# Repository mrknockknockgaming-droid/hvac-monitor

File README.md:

# Fullscope: continuous HVAC diagnostics

Fullscope monitors a home's heat pump or air conditioner continuously, the way a technician
would with gauges on it, and tells the contractor and the homeowner when something is going
wrong, before it becomes a no-cool call.

Two small ESP32 monitors sit on the equipment:
- **Outdoor:** refrigerant pressures, line temperatures, outdoor air.
- **Indoor:** supply and return air.

Both read which calls the thermostat is making. A cloud service turns their readings into
superheat, subcooling, delta-T and other checks, and shows them in a web app with two views:
- a **technician view** with live trends and diagnostics;
- a **homeowner view** in plain language.

## Status (October 2026)

| Part | State |
|---|---|
| Node firmware (outdoor + indoor) | v0.2.0 built; both dev boards online running 0.1.0, 0.2.0 goes on at board bring-up |
| Carrier boards (rev A, KiCad) | Arrived and assembled; all sensors arrived, enclosures next |
| Cloud + web app | Working locally (SQLite) and in Docker (TimescaleDB); production setup ready to deploy |
| Contractor demo | Seven scripted homes for customer interviews |
| Display thermostat (add-on) | Cloud side, screen and firmware written and tested on the PC; no hardware yet |
| Electrical module (add-on) | Diagnostics written; no hardware yet |
| 900 MHz LoRa radio | Designed and written (nodes, gateway, thermostat as gateway); waiting on a range test |

The full plan is in [project-files/1-plans/roadmap.md](project-files/1-plans/roadmap.md).

## How it fits together

```
 outdoor node ─┐                       ┌─ web app: homeowner + technician views, fleet page
 indoor node  ─┼─ WiFi (or LoRa via ─▶ MQTT broker ─▶ cloud: ingest → diagnostics → alerts
 thermostat   ─┘   a gateway)                          (FastAPI, SQLite / TimescaleDB)
                                                       └─ email alerts, thermostat config + display feed
```

- The nodes publish JSON on `hvac/<site>/<node>/{telemetry,status,reply}` and take
  calibration commands on `.../cmd`.
- The cloud judges each check only when it can be judged, for example refrigerant after
  10 minutes of steady running. A problem that lasts 5 minutes raises an alert.
- The optional display thermostat runs all its control and safety logic on the device itself,
  so heating and cooling never depend on the internet.

## What's where

| Folder | What it is |
|---|---|
| [hvac-firmware](hvac-firmware) | ESP32 firmware for the outdoor and indoor nodes (PlatformIO) |
| [hvac-cloud](hvac-cloud) | Cloud: MQTT ingest, diagnostics, alerts, REST API, the Fullscope web app, contractor demo, Docker / production setup ([DEPLOY.md](hvac-cloud/DEPLOY.md)) |
| [hvac-monitor-app](hvac-monitor-app) | PC dashboard for bench work with one system |
| [hardware](hardware) | Rev A carrier boards (KiCad, fabrication files, schematic PDFs) |
| [docs](docs) | Wiring schematics and carrier-board notes (HTML) |
| [thermostat](thermostat) | Display thermostat: design ([README](thermostat/README.md)) and firmware for the Waveshare ESP32-S3 4.3" board |
| [electrical](electrical) | Electrical monitoring module: design and diagnostic rules |
| [radio](radio) | 900 MHz LoRa: FCC research, frame format, Python reference, C++ library, gateway, range test |
| [design](design) | Fullscope design system, mockups and logos |
| [project-files](project-files) | Roadmap, contractor interview kit, parts list, screenshots, branding |
| [_archive](_archive) | Early prototypes, kept for reference |

[CLAUDE.md](CLAUDE.md) is the detailed, up-to-date technical overview of the whole project.

## Running it

**On Windows, the quick way:** `start-hvac.bat` (the Desktop "HVAC Monitor" shortcut) starts
three things:
- the MQTT broker;
- the PC dashboard on http://localhost:8080;
- the cloud with its web app on http://localhost:8000.

**Cloud only, for development:**

```powershell
cd hvac-cloud
python -m venv .venv
.venv\Scripts\python.exe -m pip install -r requirements-dev.txt
.venv\Scripts\python.exe -m pytest -q
```

Then follow [hvac-cloud/README.md](hvac-cloud/README.md) to create an account and system and
start the ingest worker and API.

**The contractor demo:** after the cloud is running, `hvac-cloud\start-demo.bat` creates a demo
contractor account with seven homes acting out common faults. The sign-ins are saved to
`hvac-cloud\demo-login.txt`.

**Firmware:** copy `include/config.example.h` to `include/config.h`, fill in WiFi and the
broker, then build and flash with PlatformIO:

```powershell
cd hvac-firmware
pio run -e outdoor -t upload
```

See [hvac-firmware/README.md](hvac-firmware/README.md) for calibration and the command list.

## Tests

| Where | Command | What it checks |
|---|---|---|
| `hvac-cloud` | `.venv\Scripts\python.exe -m pytest -q` | Cloud, diagnostics, alerts, accounts, thermostat, demo |
| `thermostat/firmware` | `pio test -e native` | The thermostat's C++ controller replayed against the Python reference |
| `radio/lora` | `pio test -e native` | LoRa frames and encryption, byte for byte against the Python reference |
| `radio` | `.venv\Scripts\python.exe -m pytest -q` | The Python frame format reference |

The native PlatformIO tests need a host C++ compiler, for example MSYS2 `ucrt64` on the PATH.

## Safety

The monitors are low-voltage (24 VAC from the equipment's control circuit). Never connect a
board to USB and 24 VAC at the same time. The electrical module and the thermostat touch more
than that, and their READMEs cover what is needed before either goes near real equipment
(isolation, qualified installation, UL 60730 / 61010). Readings are diagnostic inferences, not
confirmed diagnoses.

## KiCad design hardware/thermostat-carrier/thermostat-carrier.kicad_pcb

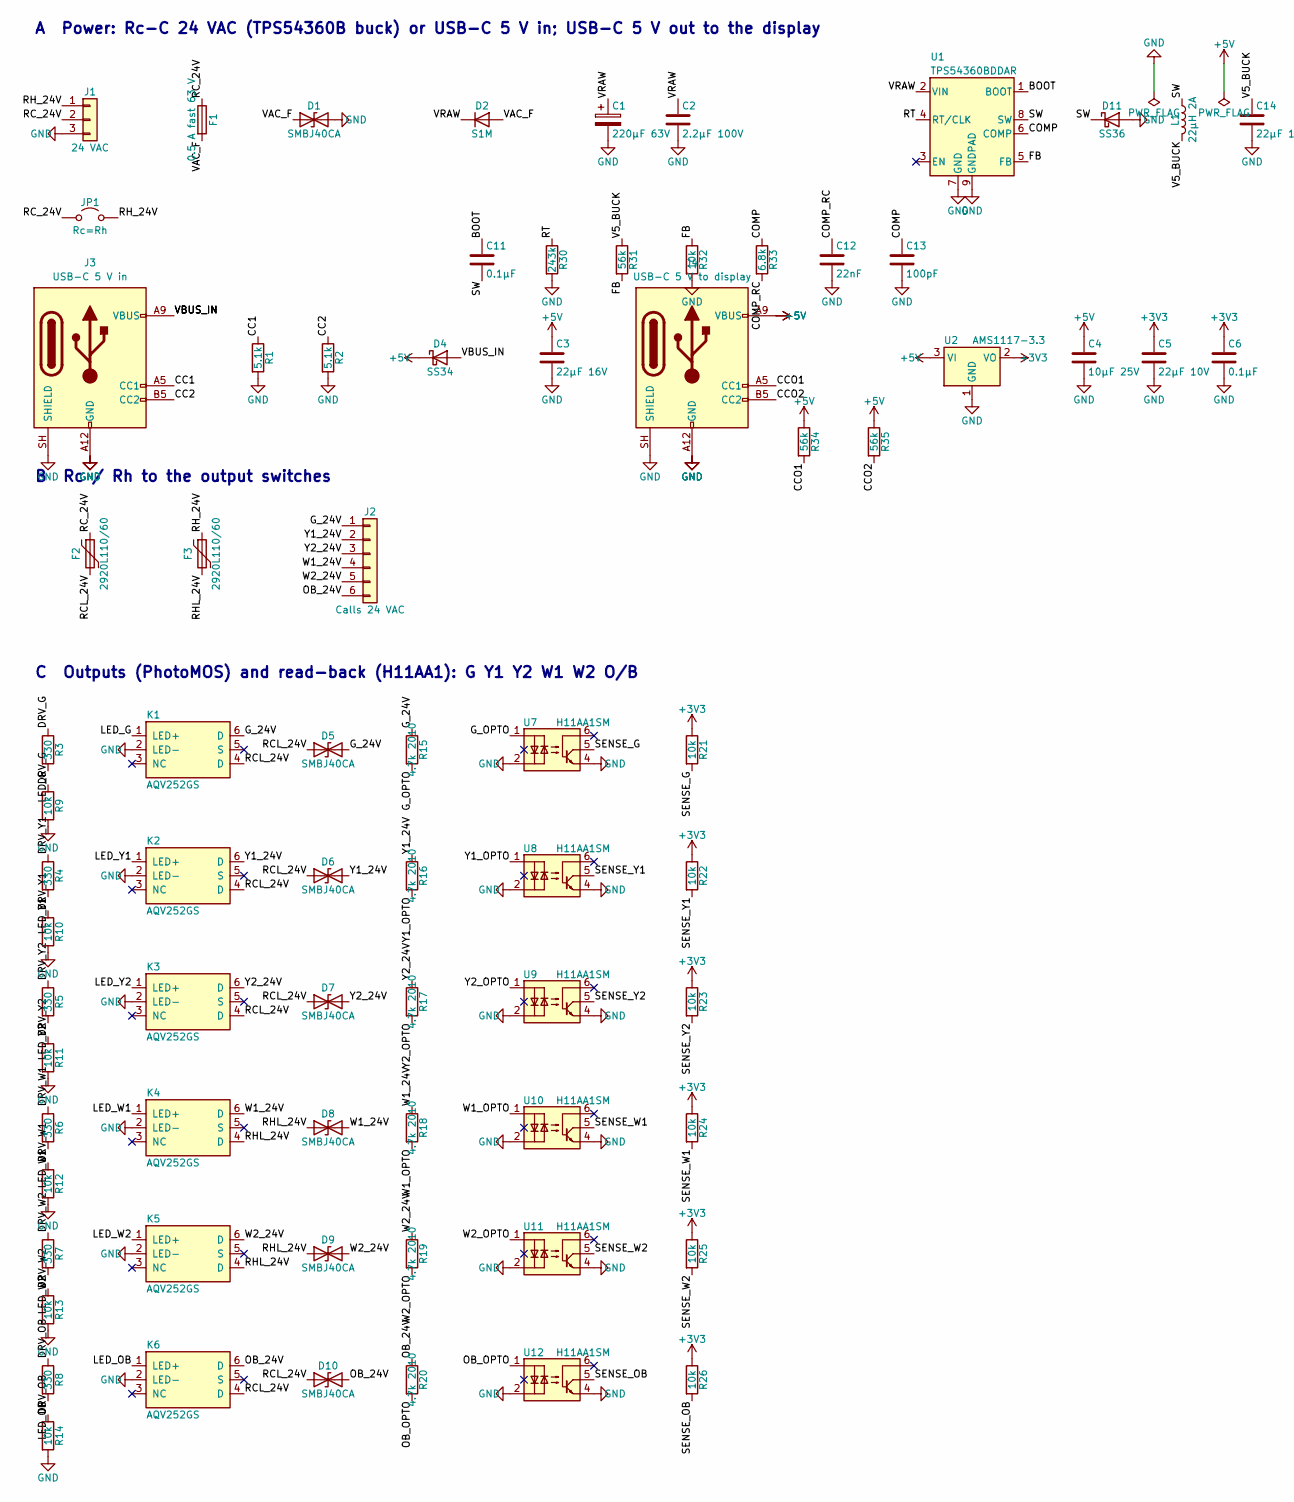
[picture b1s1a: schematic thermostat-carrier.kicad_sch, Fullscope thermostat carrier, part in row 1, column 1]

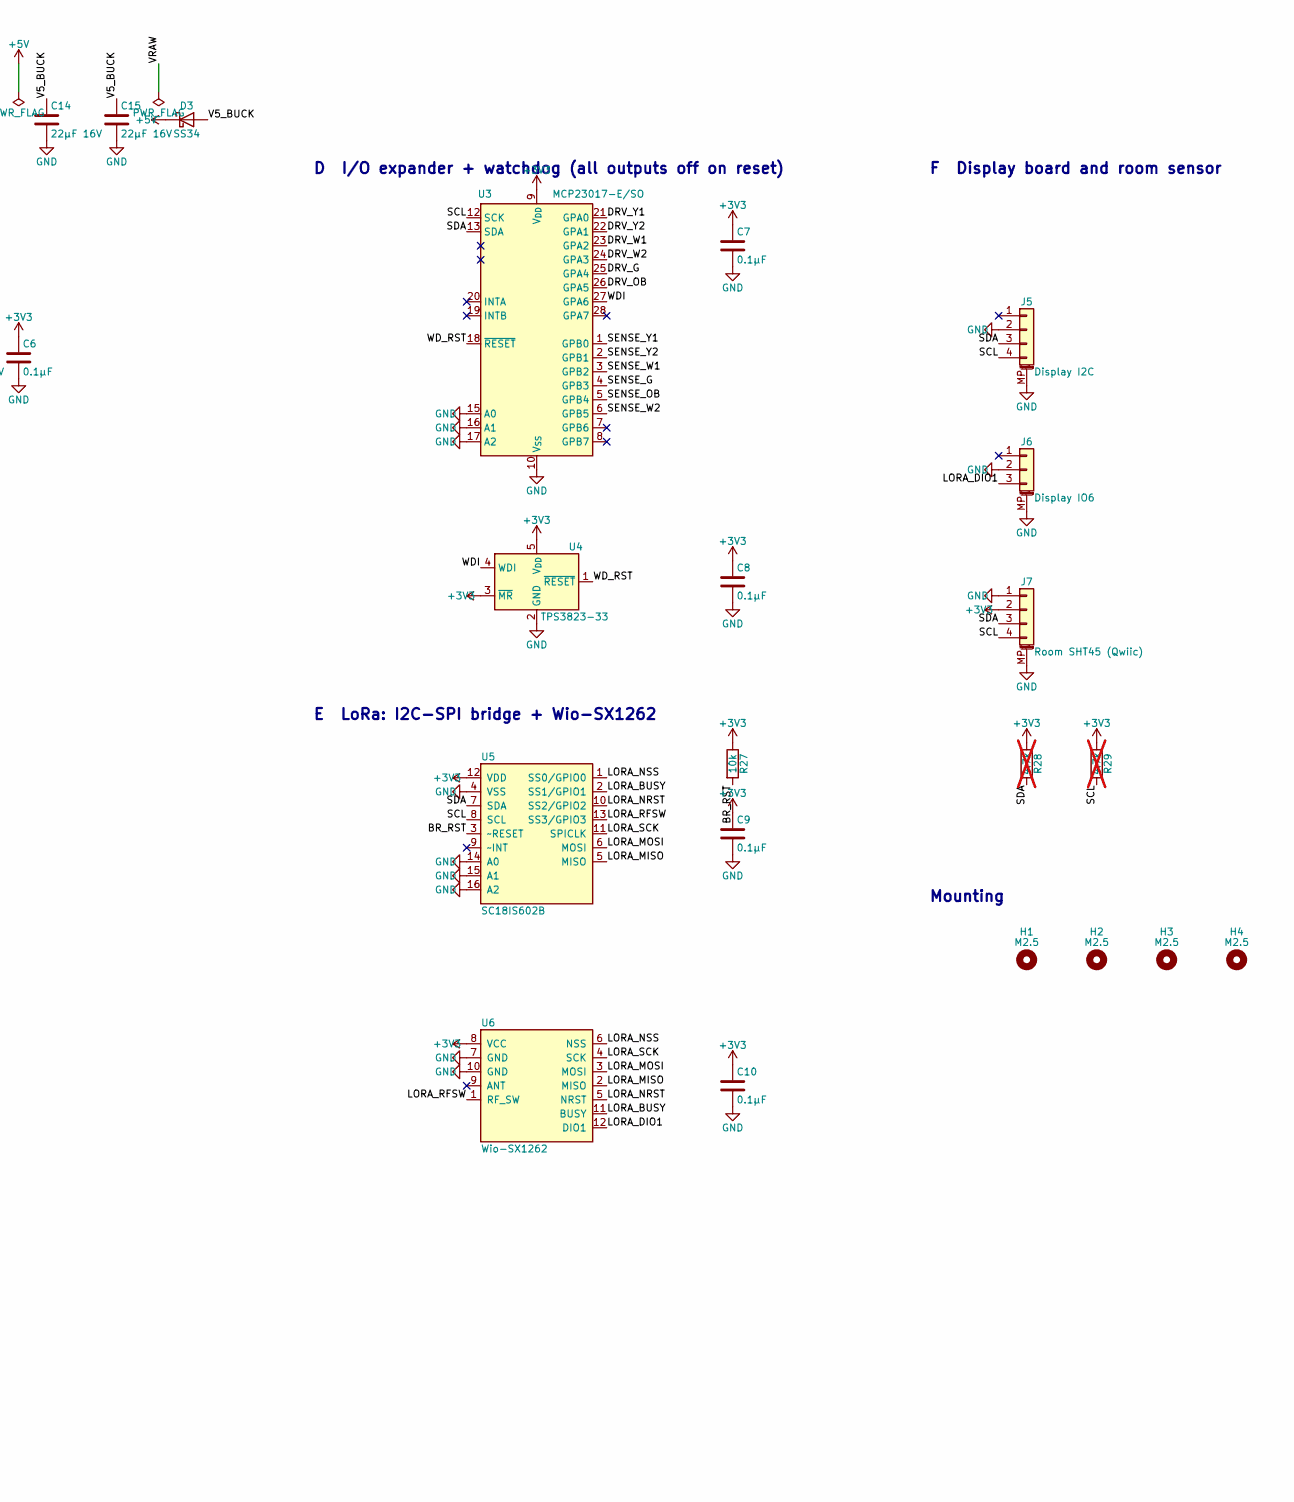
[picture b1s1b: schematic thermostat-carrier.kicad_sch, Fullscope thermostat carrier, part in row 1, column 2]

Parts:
C1: 220µF 63V; CP_Elec_10x10.5
C2: 2.2µF 100V; C_1210_3225Metric
C3, C14, C15: 22µF 16V; C_1206_3216Metric
C4: 10µF 25V; C_0805_2012Metric
C5: 22µF 10V; C_0805_2012Metric
C6, C7, C8, C9, C10, C11: 0.1µF; C_0805_2012Metric
C12: 22nF; C_0805_2012Metric
C13: 100pF; C_0805_2012Metric
D1, D5, D6, D7, D8, D9, D10: SMBJ40CA; D_SMB
D2: S1M; D_SMA
D3, D4: SS34; D_SMA
D11: SS36; D_SMA
F1: 0.5 A fast 63 V; Fuse_1206_3216Metric
F2, F3: 2920L110/60; Fuse_2920_7451Metric
H1, H2, H3, H4: M2.5; MountingHole_2.7mm_M2.5_DIN965
J1: 24 VAC; PhoenixContact_MCV_1,5_3-G-3.5_1x03_P3.50mm_Vertical
J2: Calls 24 VAC; PhoenixContact_MCV_1,5_6-G-3.5_1x06_P3.50mm_Vertical
J3: USB-C 5 V in; USB_C_Receptacle_GCT_USB4125-xx-x_6P_TopMnt_Horizontal
J4: USB-C 5 V to display; USB_C_Receptacle_GCT_USB4125-xx-x_6P_TopMnt_Horizontal
J5: Display I2C; JST_PH_B4B-PH-SM4-TB_1x04-1MP_P2.00mm_Vertical
J6: Display IO6; JST_PH_B3B-PH-SM4-TB_1x03-1MP_P2.00mm_Vertical
J7: Room SHT45 (Qwiic); JST_SH_SM04B-SRSS-TB_1x04-1MP_P1.00mm_Horizontal
JP1: Rc=Rh; PinHeader_1x02_P2.54mm_Vertical
K1, K2, K3, K4, K5, K6: AQV252GS; SMDIP-6_W9.53mm
L1: 22µH 2A; L_7.3x7.3_H4.5
R1, R2: 5.1k; R_0805_2012Metric
R3, R4, R5, R6, R7, R8: 330; R_0805_2012Metric
R9, R10, R11, R12, R13, R14, R21, R22, R23, R24, R25, R26, R27, R32: 10k; R_0805_2012Metric
R15, R16, R17, R18, R19, R20: 4.7k 2010; R_2010_5025Metric
R28, R29: 4.7k; R_0805_2012Metric; not fitted
R30: 243k; R_0805_2012Metric
R31, R34, R35: 56k; R_0805_2012Metric
R33: 6.8k; R_0805_2012Metric
U1: TPS54360BDDAR; TI_SO-PowerPAD-8_ThermalVias
U2: AMS1117-3.3; SOT-223-3_TabPin2
U3: MCP23017-E/SO; SOIC-28W_7.5x17.9mm_P1.27mm
U4: TPS3823-33; SOT-23-5
U5: SC18IS602B; TSSOP-16_4.4x5mm_P0.65mm
U6: Wio-SX1262; Wio_SX1262
U7, U8, U9, U10, U11, U12: H11AA1SM; SMDIP-6_W9.53mm

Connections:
+3V3: C5.1, C6.1, C7.1, C8.1, C9.1, C10.1, J7.2, R21.1, R22.1, R23.1, R24.1, R25.1, R26.1, R27.1, R28.1, R29.1, U2.2 (VO), U3.9 (V_{DD}), U4.3 (~MR), U4.5 (V_{DD}), U5.12 (VDD), U6.8 (VCC)
+5V: C3.1, C4.1, D3.1 (K), D4.1 (K), J4.A9 (VBUS), J4.B9 (VBUS), R34.1, R35.1, U2.3 (VI)
/BOOT: C11.1, U1.1 (BOOT)
/BR_RST: R27.2, U5.3 (~RESET)
/CC1: J3.A5 (CC1), R1.1
/CC2: J3.B5 (CC2), R2.1
/CCO1: J4.A5 (CC1), R34.2
/CCO2: J4.B5 (CC2), R35.2
/COMP: C13.1, R33.1, U1.6 (COMP)
/COMP_RC: C12.1, R33.2
/DRV_G: R3.1, R9.1, U3.25 (GPA4)
/DRV_OB: R8.1, R14.1, U3.26 (GPA5)
/DRV_W1: R6.1, R12.1, U3.23 (GPA2)
/DRV_W2: R7.1, R13.1, U3.24 (GPA3)
/DRV_Y1: R4.1, R10.1, U3.21 (GPA0)
/DRV_Y2: R5.1, R11.1, U3.22 (GPA1)
/FB: R31.2, R32.1, U1.5 (FB)
/G_24V: D5.2 (A2), J2.1, K1.6 (D), R15.1
/G_OPTO: R15.2, U7.1
/LED_G: K1.1 (LED+), R3.2
/LED_OB: K6.1 (LED+), R8.2
/LED_W1: K4.1 (LED+), R6.2
/LED_W2: K5.1 (LED+), R7.2
/LED_Y1: K2.1 (LED+), R4.2
/LED_Y2: K3.1 (LED+), R5.2
/LORA_BUSY: U5.2 (SS1/GPIO1), U6.11 (BUSY)
/LORA_DIO1: J6.3, U6.12 (DIO1)
/LORA_MISO: U5.5 (MISO), U6.2 (MISO)
/LORA_MOSI: U5.6 (MOSI), U6.3 (MOSI)
/LORA_NRST: U5.10 (SS2/GPIO2), U6.5 (NRST)
/LORA_NSS: U5.1 (SS0/GPIO0), U6.6 (NSS)
/LORA_RFSW: U5.13 (SS3/GPIO3), U6.1 (RF_SW)
/LORA_SCK: U5.11 (SPICLK), U6.4 (SCK)
/OB_24V: D10.2 (A2), J2.6, K6.6 (D), R20.1
/OB_OPTO: R20.2, U12.1
/RCL_24V: D5.1 (A1), D6.1 (A1), D7.1 (A1), D10.1 (A1), F2.2, K1.4 (D), K2.4 (D), K3.4 (D), K6.4 (D)
/RC_24V: F1.1, F2.1, J1.2, JP1.1 (A)
/RHL_24V: D8.1 (A1), D9.1 (A1), F3.2, K4.4 (D), K5.4 (D)
/RH_24V: F3.1, J1.1, JP1.2 (B)
/RT: R30.1, U1.4 (RT/CLK)
/SCL: J5.4, J7.4, R29.2, U3.12 (SCK), U5.8 (SCL)
/SDA: J5.3, J7.3, R28.2, U3.13 (SDA), U5.7 (SDA)
/SENSE_G: R21.2, U3.4 (GPB3), U7.5
/SENSE_OB: R26.2, U3.5 (GPB4), U12.5
/SENSE_W1: R24.2, U3.3 (GPB2), U10.5
/SENSE_W2: R25.2, U3.6 (GPB5), U11.5
/SENSE_Y1: R22.2, U3.1 (GPB0), U8.5
/SENSE_Y2: R23.2, U3.2 (GPB1), U9.5
/SW: C11.2, D11.1 (K), L1.1, U1.8 (SW)
/V5_BUCK: C14.1, C15.1, D3.2 (A), L1.2, R31.1
/VAC_F: D1.1 (A1), D2.2 (A), F1.2
/VBUS_IN: D4.2 (A), J3.A9 (VBUS), J3.B9 (VBUS)
/VRAW: C1.1, C2.1, D2.1 (K), U1.2 (VIN)
/W1_24V: D8.2 (A2), J2.4, K4.6 (D), R18.1
/W1_OPTO: R18.2, U10.1
/W2_24V: D9.2 (A2), J2.5, K5.6 (D), R19.1
/W2_OPTO: R19.2, U11.1
/WDI: U3.27 (GPA6), U4.4 (WDI)
/WD_RST: U3.18 (~RESET), U4.1 (~RESET)
/Y1_24V: D6.2 (A2), J2.2, K2.6 (D), R16.1
/Y1_OPTO: R16.2, U8.1
/Y2_24V: D7.2 (A2), J2.3, K3.6 (D), R17.1
/Y2_OPTO: R17.2, U9.1
GND: C1.2, C2.2, C3.2, C4.2, C5.2, C6.2, C7.2, C8.2, C9.2, C10.2, C12.2, C13.2, C14.2, C15.2, D1.2 (A2), D11.2 (A), J1.3, J3.A12 (GND), J3.B12 (GND), J3.SH (SHIELD), J4.A12 (GND), J4.B12 (GND), J4.SH (SHIELD), J5.2, J5.MP (MountPin), J6.2, J6.MP (MountPin), J7.1, J7.MP (MountPin), K1.2 (LED−), K2.2 (LED−), K3.2 (LED−), K4.2 (LED−), K5.2 (LED−), K6.2 (LED−), R1.2, R2.2, R9.2, R10.2, R11.2, R12.2, R13.2, R14.2, R30.2, R32.2, U1.7 (GND), U1.9 (GNDPAD), U2.1 (GND), U3.10 (V_{SS}), U3.15 (A0), U3.16 (A1), U3.17 (A2), U4.2 (GND), U5.4 (VSS), U5.14 (A0), U5.15 (A1), U5.16 (A2), U6.7 (GND), U6.10 (GND), U7.2, U7.4, U8.2, U8.4, U9.2, U9.4, U10.2, U10.4, U11.2, U11.4, U12.2, U12.4

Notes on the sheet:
A Power: Rc-C 24 VAC (TPS54360B buck) or USB-C 5 V in; USB-C 5 V out to the display
B Rc / Rh to the output switches
C Outputs (PhotoMOS) and read-back (H11AA1): G Y1 Y2 W1 W2 O/B
D I/O expander + watchdog (all outputs off on reset)
E LoRa: I2C-SPI bridge + Wio-SX1262
F Display board and room sensor
Mounting

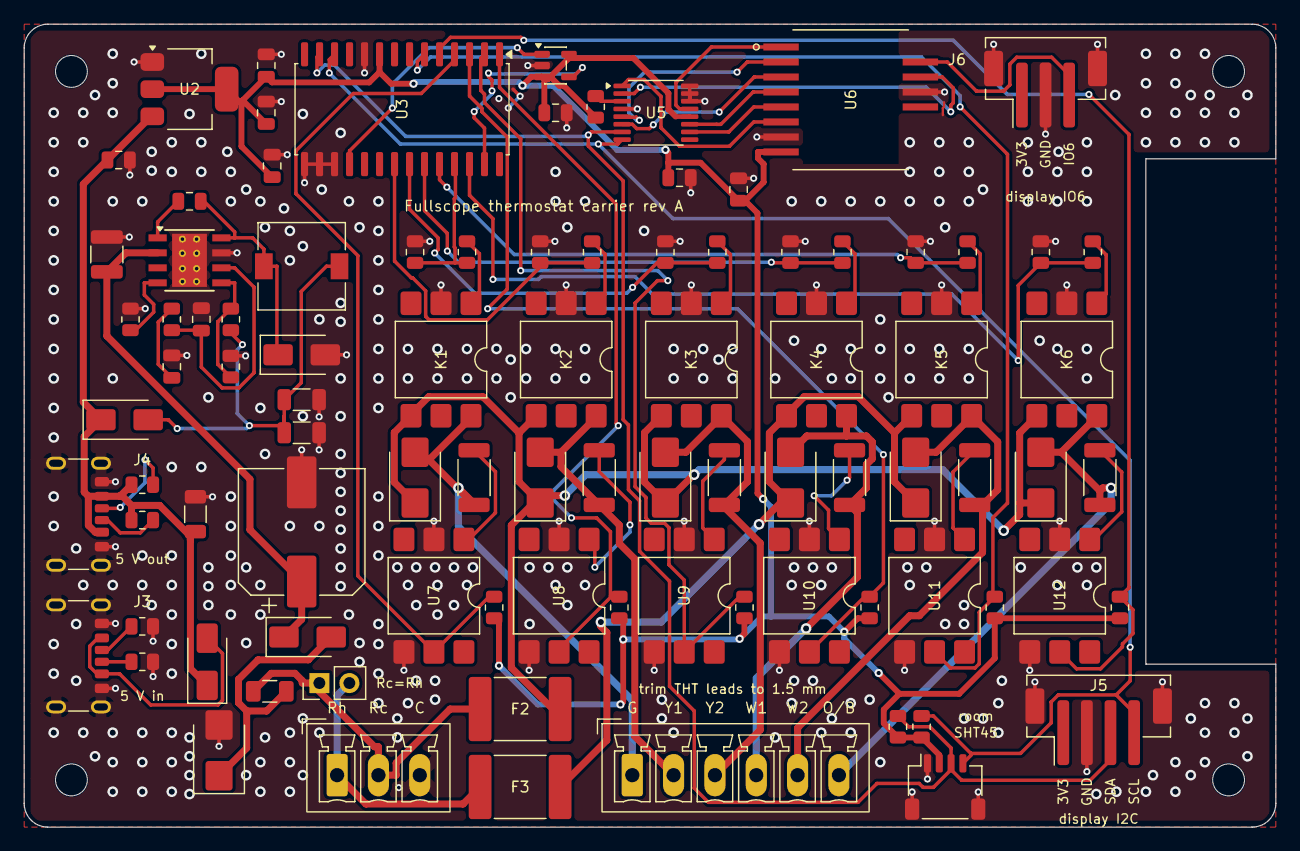
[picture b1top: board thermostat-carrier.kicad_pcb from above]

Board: 2 copper layers, 106.0 x 68.0 mm, 95 parts (0 on the bottom side), 64 nets.

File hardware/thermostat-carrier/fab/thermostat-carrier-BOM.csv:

"Refs","Value","Footprint","Qty","DNP","Off-board"
"C1","220µF 63V","Capacitor_SMD:CP_Elec_10x10.5","1","",""
"C2","2.2µF 100V","Capacitor_SMD:C_1210_3225Metric","1","",""
"C3,C14,C15","22µF 16V","Capacitor_SMD:C_1206_3216Metric","3","",""
"C4","10µF 25V","Capacitor_SMD:C_0805_2012Metric","1","",""
"C5","22µF 10V","Capacitor_SMD:C_0805_2012Metric","1","",""
"C6-C11","0.1µF","Capacitor_SMD:C_0805_2012Metric","6","",""
"C12","22nF","Capacitor_SMD:C_0805_2012Metric","1","",""
"C13","100pF","Capacitor_SMD:C_0805_2012Metric","1","",""
"D1,D5-D10","SMBJ40CA","Diode_SMD:D_SMB","7","",""
"D2","S1M","Diode_SMD:D_SMA","1","",""
"D3,D4","SS34","Diode_SMD:D_SMA","2","",""
"D11","SS36","Diode_SMD:D_SMA","1","",""
"F1","0.5 A fast 63 V","Fuse:Fuse_1206_3216Metric","1","",""
"F2,F3","2920L110/60","Fuse:Fuse_2920_7451Metric","2","",""
"J1","24 VAC","Connector_Phoenix_MC:PhoenixContact_MCV_1,5_3-G-3.5_1x03_P3.50mm_Vertical","1","",""
"J2","Calls 24 VAC","Connector_Phoenix_MC:PhoenixContact_MCV_1,5_6-G-3.5_1x06_P3.50mm_Vertical","1","",""
"J3","USB-C 5 V in","Connector_USB:USB_C_Receptacle_GCT_USB4125-xx-x_6P_TopMnt_Horizontal","1","",""
"J4","USB-C 5 V to display","Connector_USB:USB_C_Receptacle_GCT_USB4125-xx-x_6P_TopMnt_Horizontal","1","",""
"J5","Display I2C","Connector_JST:JST_PH_B4B-PH-SM4-TB_1x04-1MP_P2.00mm_Vertical","1","",""
"J6","Display IO6","Connector_JST:JST_PH_B3B-PH-SM4-TB_1x03-1MP_P2.00mm_Vertical","1","",""
"J7","Room SHT45 (Qwiic)","Connector_JST:JST_SH_SM04B-SRSS-TB_1x04-1MP_P1.00mm_Horizontal","1","",""
"JP1","Rc=Rh","Connector_PinHeader_2.54mm:PinHeader_1x02_P2.54mm_Vertical","1","",""
"K1-K6","AQV252GS","Package_DIP:SMDIP-6_W9.53mm","6","",""
"L1","22µH 2A","Inductor_SMD:L_7.3x7.3_H4.5","1","",""
"R1,R2","5.1k","Resistor_SMD:R_0805_2012Metric","2","",""
"R3-R8","330","Resistor_SMD:R_0805_2012Metric","6","",""
"R9-R14,R21-R27,R32","10k","Resistor_SMD:R_0805_2012Metric","14","",""
"R15-R20","4.7k 2010","Resistor_SMD:R_2010_5025Metric","6","",""
"R28,R29","4.7k","Resistor_SMD:R_0805_2012Metric","2","DNP",""
"R30","243k","Resistor_SMD:R_0805_2012Metric","1","",""
"R31,R34,R35","56k","Resistor_SMD:R_0805_2012Metric","3","",""
"R33","6.8k","Resistor_SMD:R_0805_2012Metric","1","",""
"U1","TPS54360BDDAR","Package_SO:TI_SO-PowerPAD-8_ThermalVias","1","",""
"U2","AMS1117-3.3","Package_TO_SOT_SMD:SOT-223-3_TabPin2","1","",""
"U3","MCP23017-E/SO","Package_SO:SOIC-28W_7.5x17.9mm_P1.27mm","1","",""
"U4","TPS3823-33","Package_TO_SOT_SMD:SOT-23-5","1","",""
"U5","SC18IS602B","Package_SO:TSSOP-16_4.4x5mm_P0.65mm","1","",""
"U6","Wio-SX1262","hvac_carrier:Wio_SX1262","1","",""
"U7-U12","H11AA1SM","Package_DIP:SMDIP-6_W9.53mm","6","",""

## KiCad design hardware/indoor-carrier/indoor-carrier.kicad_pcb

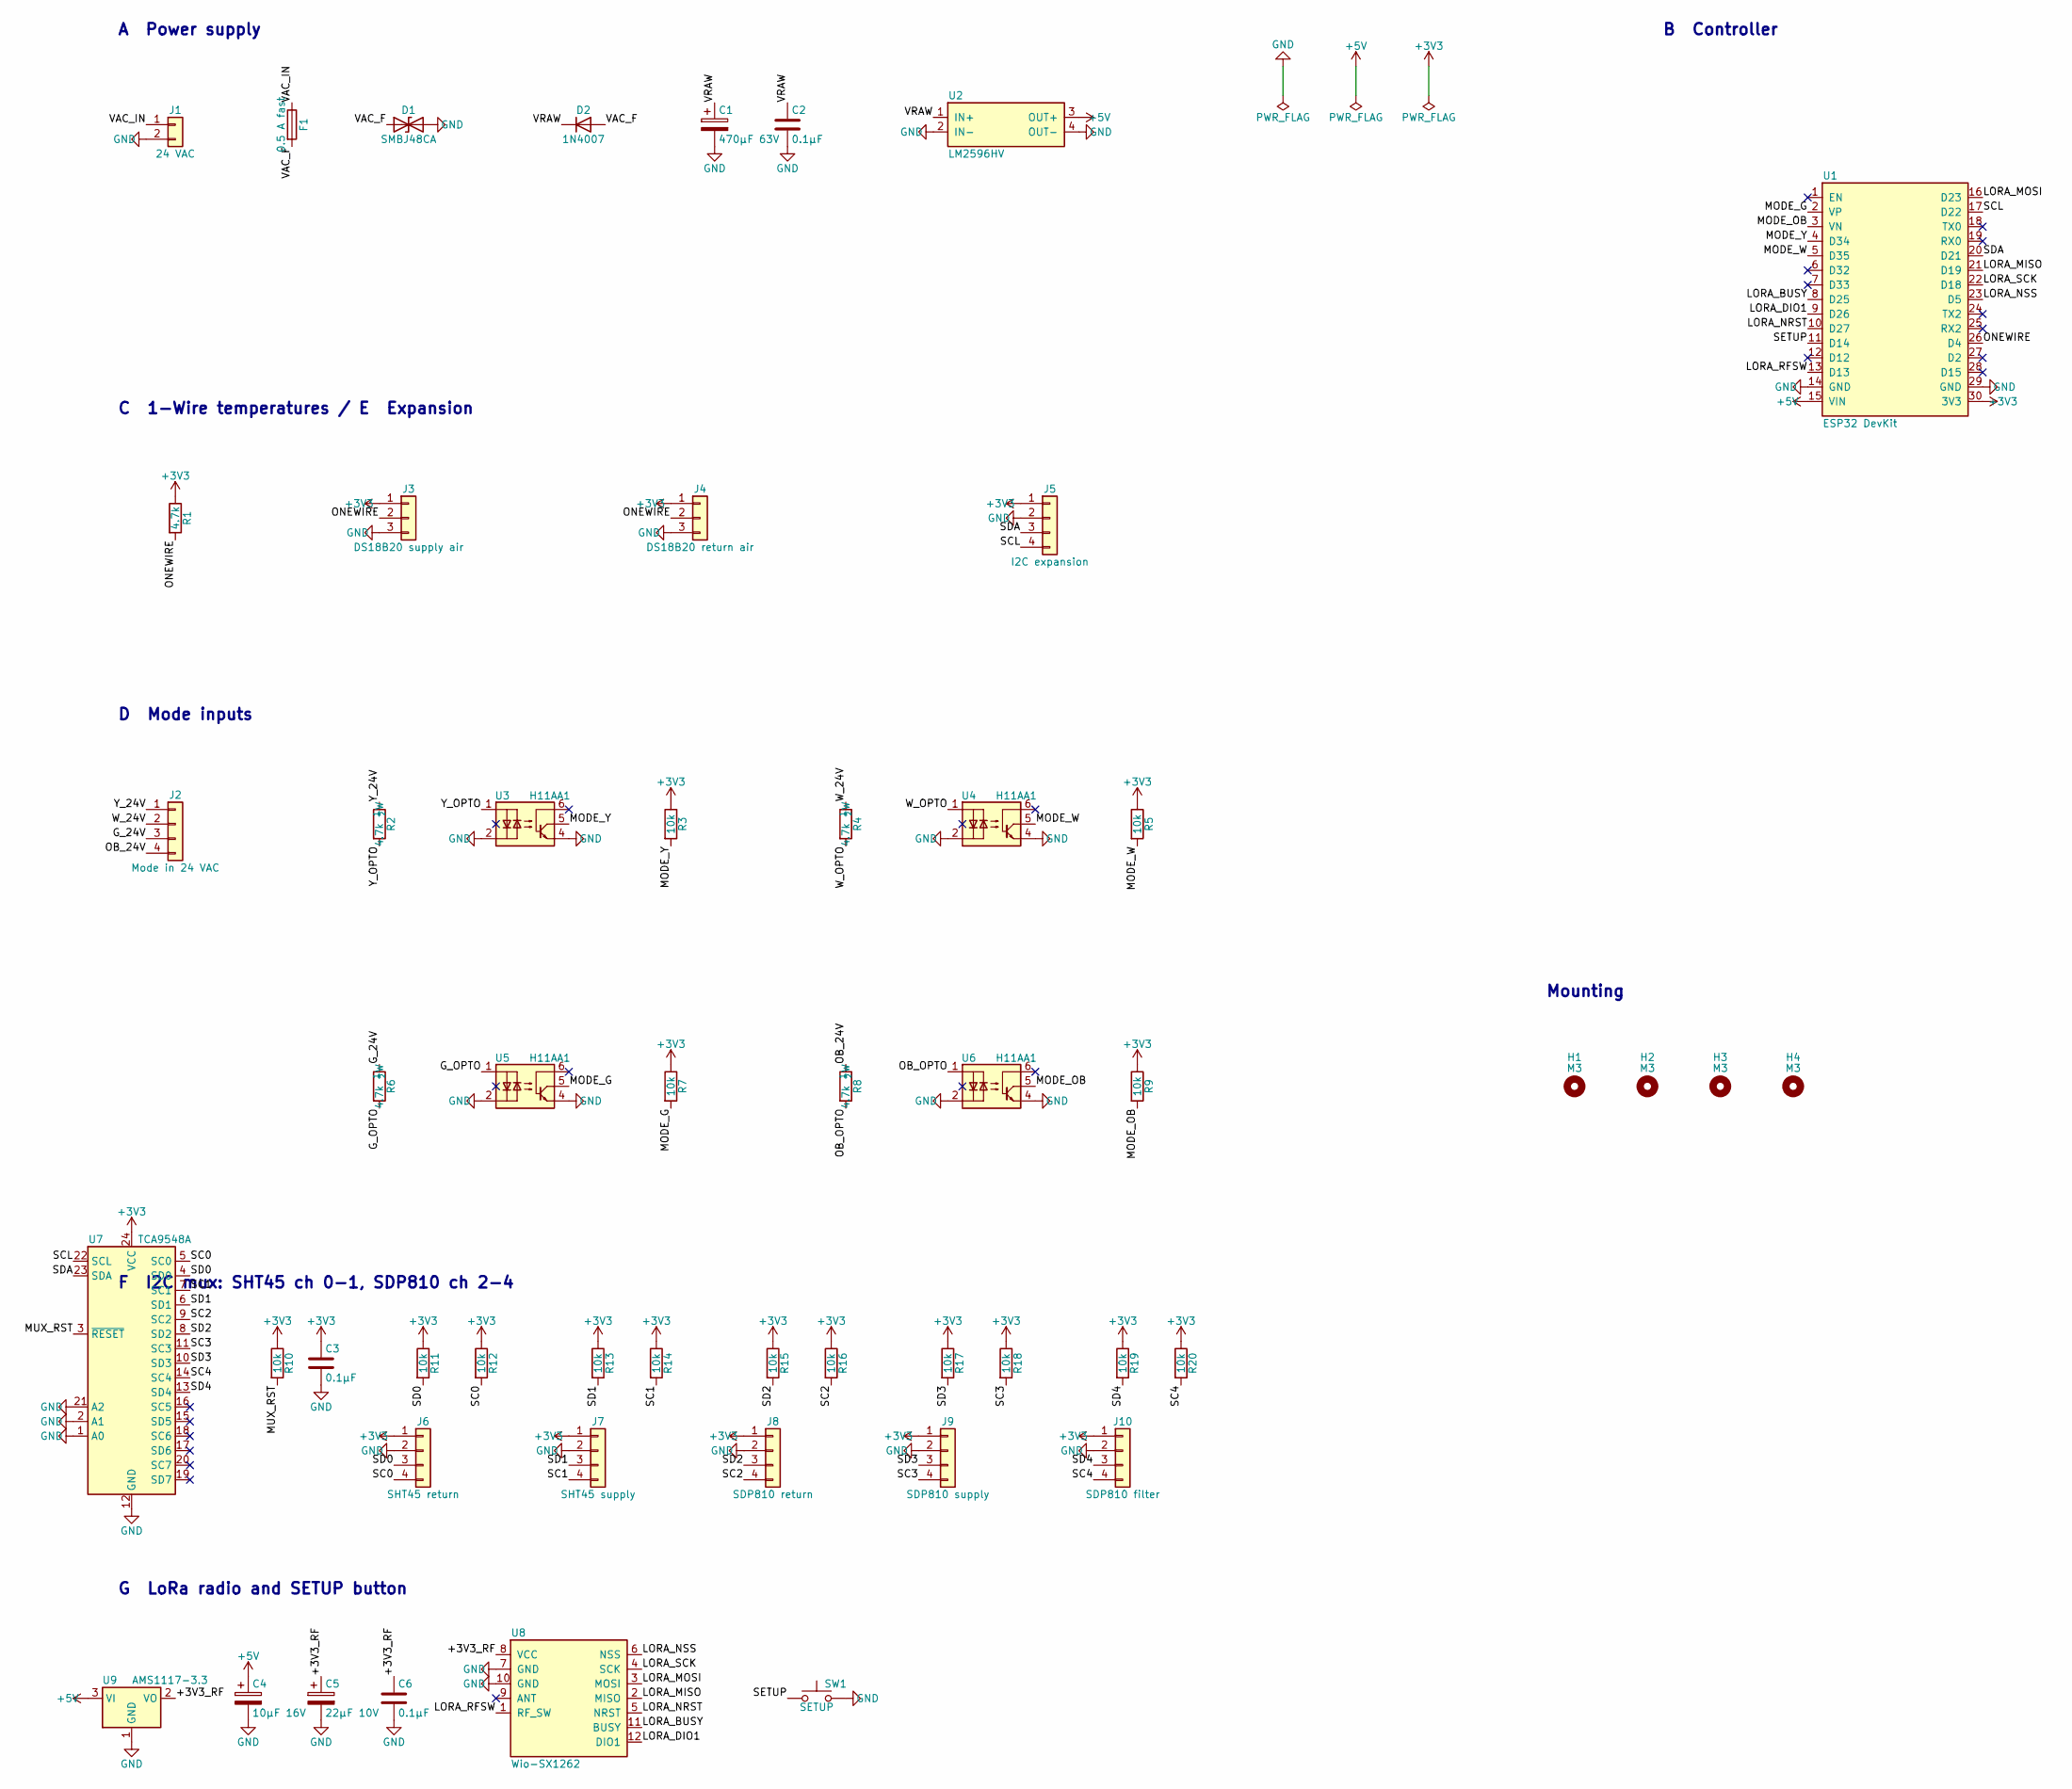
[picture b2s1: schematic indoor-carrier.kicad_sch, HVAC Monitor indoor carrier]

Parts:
C1: 470µF 63V; CP_Radial_D10.0mm_P5.00mm
C2, C6: 0.1µF; C_Disc_D5.0mm_W2.5mm_P2.50mm
C3: 0.1µF; C_0805_2012Metric_Pad1.18x1.45mm_HandSolder
C4: 10µF 16V; CP_Radial_D5.0mm_P2.00mm
C5: 22µF 10V; CP_Radial_D5.0mm_P2.00mm
D1: SMBJ48CA; D_SMB_Handsoldering
D2: 1N4007; D_DO-41_SOD81_P10.16mm_Horizontal
F1: 0.5 A fast; Fuseholder_Clip-5x20mm_Littelfuse_111_Inline_P20.00x5.00mm_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
H1, H2, H3, H4: M3; MountingHole_3.2mm_M3_DIN965
J1: 24 VAC; PhoenixContact_MC_1,5_2-G-5.08_1x02_P5.08mm_Horizontal
J2: Mode in 24 VAC; PhoenixContact_MC_1,5_4-G-5.08_1x04_P5.08mm_Horizontal
J3: DS18B20 supply air; JST_XH_B3B-XH-A_1x03_P2.50mm_Vertical
J4: DS18B20 return air; JST_XH_B3B-XH-A_1x03_P2.50mm_Vertical
J5: I2C expansion; PhoenixContact_MC_1,5_4-G-5.08_1x04_P5.08mm_Horizontal
J6: SHT45 return; JST_XH_B4B-XH-A_1x04_P2.50mm_Vertical
J7: SHT45 supply; JST_XH_B4B-XH-A_1x04_P2.50mm_Vertical
J8: SDP810 return; JST_XH_B4B-XH-A_1x04_P2.50mm_Vertical
J9: SDP810 supply; JST_XH_B4B-XH-A_1x04_P2.50mm_Vertical
J10: SDP810 filter; JST_XH_B4B-XH-A_1x04_P2.50mm_Vertical
R1: 4.7k; R_Axial_DIN0207_L6.3mm_D2.5mm_P10.16mm_Horizontal
R2, R4, R6, R8: 4.7k ½W; R_Axial_DIN0309_L9.0mm_D3.2mm_P12.70mm_Horizontal
R3, R5, R7, R9: 10k; R_Axial_DIN0207_L6.3mm_D2.5mm_P10.16mm_Horizontal
R10, R11, R12, R13, R14, R15, R16, R17, R18, R19, R20: 10k; R_0805_2012Metric_Pad1.20x1.40mm_HandSolder
SW1: SETUP; SW_PUSH_6mm
U1: ESP32 DevKit; ESP32_DevKit_30pin_W25.4mm
U2: LM2596HV; LM2596HVS_Module
U3, U4, U5, U6: H11AA1; DIP-6_W7.62mm_Socket
U7: TCA9548A; TSSOP-24_4.4x7.8mm_P0.65mm
U8: Wio-SX1262; Wio_SX1262
U9: AMS1117-3.3; SOT-223-3_TabPin2

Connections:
+3V3: C3.1, J3.1, J4.1, J5.1, J6.1, J7.1, J8.1, J9.1, J10.1, R1.1, R3.1, R5.1, R7.1, R9.1, R10.1, R11.1, R12.1, R13.1, R14.1, R15.1, R16.1, R17.1, R18.1, R19.1, R20.1, U1.30 (3V3), U7.24 (VCC)
+5V: C4.1, U1.15 (VIN), U2.3 (OUT+), U9.3 (VI)
/+3V3_RF: C5.1, C6.1, U8.8 (VCC), U9.2 (VO)
/G_24V: J2.3, R6.1
/G_OPTO: R6.2, U5.1
/LORA_BUSY: U1.8 (D25), U8.11 (BUSY)
/LORA_DIO1: U1.9 (D26), U8.12 (DIO1)
/LORA_MISO: U1.21 (D19), U8.2 (MISO)
/LORA_MOSI: U1.16 (D23), U8.3 (MOSI)
/LORA_NRST: U1.10 (D27), U8.5 (NRST)
/LORA_NSS: U1.23 (D5), U8.6 (NSS)
/LORA_RFSW: U1.13 (D13), U8.1 (RF_SW)
/LORA_SCK: U1.22 (D18), U8.4 (SCK)
/MODE_G: R7.2, U1.2 (VP), U5.5
/MODE_OB: R9.2, U1.3 (VN), U6.5
/MODE_W: R5.2, U1.5 (D35), U4.5
/MODE_Y: R3.2, U1.4 (D34), U3.5
/MUX_RST: R10.2, U7.3 (~RESET)
/OB_24V: J2.4, R8.1
/OB_OPTO: R8.2, U6.1
/ONEWIRE: J3.2, J4.2, R1.2, U1.26 (D4)
/SC0: J6.4, R12.2, U7.5 (SC0)
/SC1: J7.4, R14.2, U7.7 (SC1)
/SC2: J8.4, R16.2, U7.9 (SC2)
/SC3: J9.4, R18.2, U7.11 (SC3)
/SC4: J10.4, R20.2, U7.14 (SC4)
/SCL: J5.4, U1.17 (D22), U7.22 (SCL)
/SD0: J6.3, R11.2, U7.4 (SD0)
/SD1: J7.3, R13.2, U7.6 (SD1)
/SD2: J8.3, R15.2, U7.8 (SD2)
/SD3: J9.3, R17.2, U7.10 (SD3)
/SD4: J10.3, R19.2, U7.13 (SD4)
/SDA: J5.3, U1.20 (D21), U7.23 (SDA)
/SETUP: SW1.1, U1.11 (D14)
/VAC_F: D1.1 (A1), D2.2 (A), F1.2
/VAC_IN: F1.1, J1.1
/VRAW: C1.1, C2.1, D2.1 (K), U2.1 (IN+)
/W_24V: J2.2, R4.1
/W_OPTO: R4.2, U4.1
/Y_24V: J2.1, R2.1
/Y_OPTO: R2.2, U3.1
GND: C1.2, C2.2, C3.2, C4.2, C5.2, C6.2, D1.2 (A2), J1.2, J3.3, J4.3, J5.2, J6.2, J7.2, J8.2, J9.2, J10.2, SW1.2, U1.14 (GND), U1.29 (GND), U2.2 (IN−), U2.4 (OUT−), U3.2, U3.4, U4.2, U4.4, U5.2, U5.4, U6.2, U6.4, U7.1 (A0), U7.2 (A1), U7.12 (GND), U7.21 (A2), U8.7 (GND), U8.10 (GND), U9.1 (GND)

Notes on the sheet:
A Power supply
B Controller
C 1-Wire temperatures / E Expansion
D Mode inputs
Mounting
F I2C mux: SHT45 ch 0-1, SDP810 ch 2-4
G LoRa radio and SETUP button

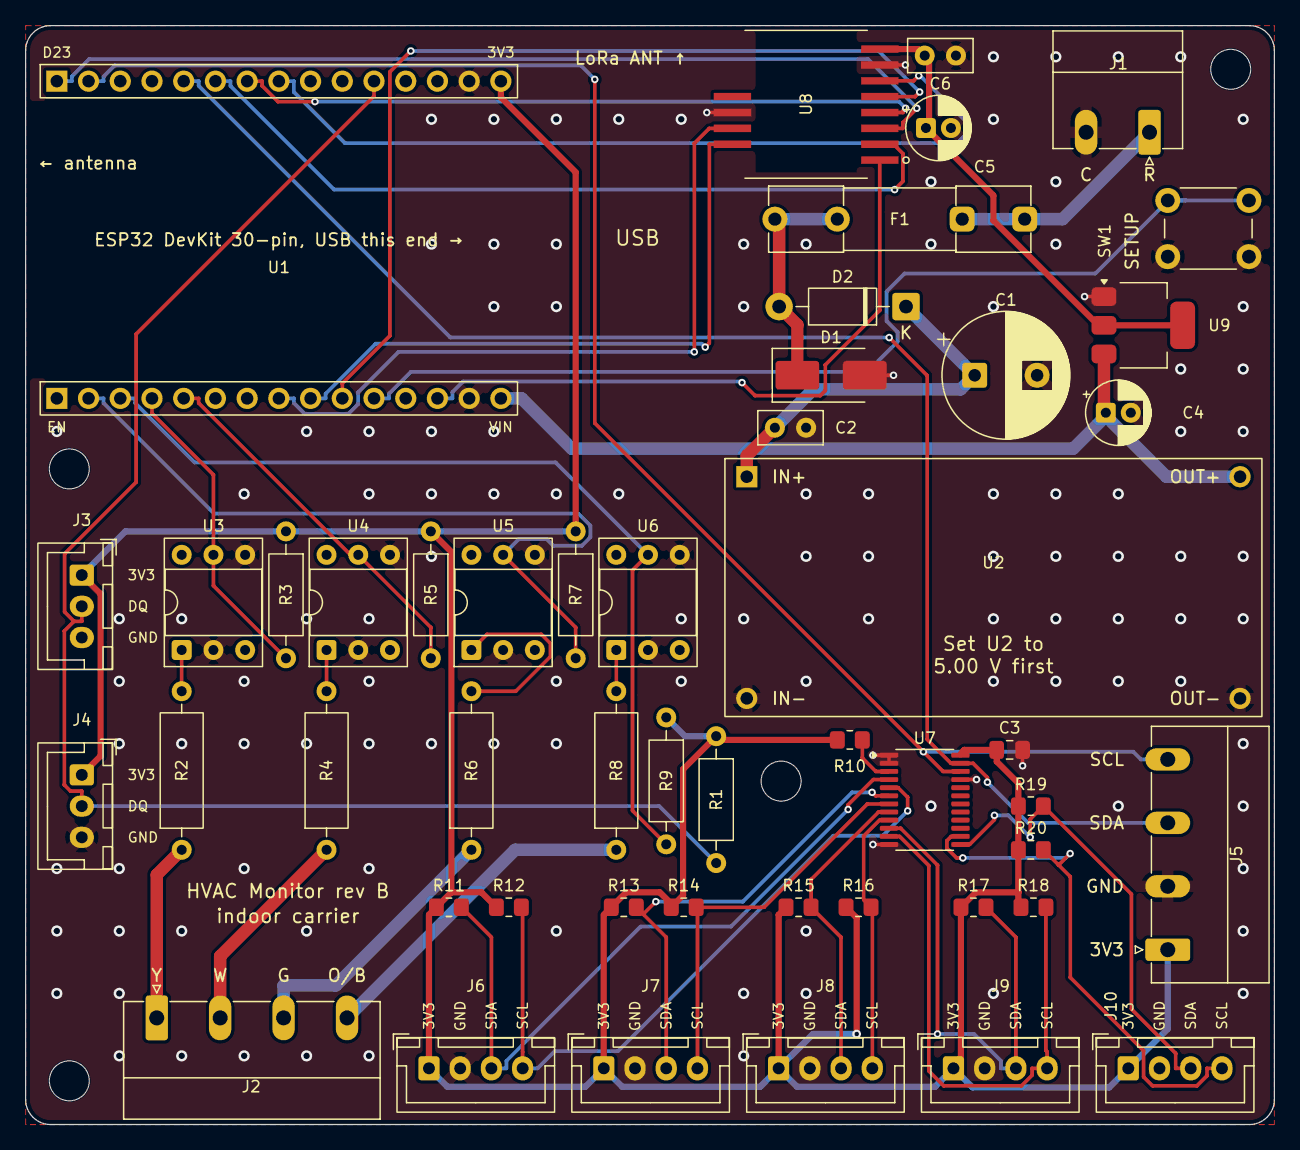
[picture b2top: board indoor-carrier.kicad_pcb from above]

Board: 2 copper layers, 100.0 x 88.0 mm, 53 parts (0 on the bottom side), 42 nets.

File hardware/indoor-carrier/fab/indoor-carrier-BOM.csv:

"Refs","Value","Footprint","Qty","DNP","Off-board"
"C1","470µF 63V","Capacitor_THT:CP_Radial_D10.0mm_P5.00mm","1","",""
"C2,C6","0.1µF","Capacitor_THT:C_Disc_D5.0mm_W2.5mm_P2.50mm","2","",""
"C3","0.1µF","Capacitor_SMD:C_0805_2012Metric_Pad1.18x1.45mm_HandSolder","1","",""
"C4","10µF 16V","Capacitor_THT:CP_Radial_D5.0mm_P2.00mm","1","",""
"C5","22µF 10V","Capacitor_THT:CP_Radial_D5.0mm_P2.00mm","1","",""
"D1","SMBJ48CA","Diode_SMD:D_SMB_Handsoldering","1","",""
"D2","1N4007","Diode_THT:D_DO-41_SOD81_P10.16mm_Horizontal","1","",""
"F1","0.5 A fast","Fuse:Fuseholder_Clip-5x20mm_Littelfuse_111_Inline_P20.00x5.00mm_D1.05mm_Horizontal","1","",""
"J1","24 VAC","Connector_Phoenix_MC_HighVoltage:PhoenixContact_MC_1,5_2-G-5.08_1x02_P5.08mm_Horizontal","1","",""
"J2","Mode in 24 VAC","Connector_Phoenix_MC_HighVoltage:PhoenixContact_MC_1,5_4-G-5.08_1x04_P5.08mm_Horizontal","1","",""
"J3","DS18B20 supply air","Connector_JST:JST_XH_B3B-XH-A_1x03_P2.50mm_Vertical","1","",""
"J4","DS18B20 return air","Connector_JST:JST_XH_B3B-XH-A_1x03_P2.50mm_Vertical","1","",""
"J5","I2C expansion","Connector_Phoenix_MC_HighVoltage:PhoenixContact_MC_1,5_4-G-5.08_1x04_P5.08mm_Horizontal","1","",""
"J6","SHT45 return","Connector_JST:JST_XH_B4B-XH-A_1x04_P2.50mm_Vertical","1","",""
"J7","SHT45 supply","Connector_JST:JST_XH_B4B-XH-A_1x04_P2.50mm_Vertical","1","",""
"J8","SDP810 return","Connector_JST:JST_XH_B4B-XH-A_1x04_P2.50mm_Vertical","1","",""
"J9","SDP810 supply","Connector_JST:JST_XH_B4B-XH-A_1x04_P2.50mm_Vertical","1","",""
"J10","SDP810 filter","Connector_JST:JST_XH_B4B-XH-A_1x04_P2.50mm_Vertical","1","",""
"R1","4.7k","Resistor_THT:R_Axial_DIN0207_L6.3mm_D2.5mm_P10.16mm_Horizontal","1","",""
"R2,R4,R6,R8","4.7k ½W","Resistor_THT:R_Axial_DIN0309_L9.0mm_D3.2mm_P12.70mm_Horizontal","4","",""
"R3,R5,R7,R9","10k","Resistor_THT:R_Axial_DIN0207_L6.3mm_D2.5mm_P10.16mm_Horizontal","4","",""
"R10-R20","10k","Resistor_SMD:R_0805_2012Metric_Pad1.20x1.40mm_HandSolder","11","",""
"SW1","SETUP","Button_Switch_THT:SW_PUSH_6mm","1","",""
"U1","ESP32 DevKit","hvac_carrier:ESP32_DevKit_30pin_W25.4mm","1","",""
"U2","LM2596HV","hvac_carrier:LM2596HVS_Module","1","",""
"U3-U6","H11AA1","Package_DIP:DIP-6_W7.62mm_Socket","4","",""
"U7","TCA9548A","Package_SO:TSSOP-24_4.4x7.8mm_P0.65mm","1","",""
"U8","Wio-SX1262","hvac_carrier:Wio_SX1262","1","",""
"U9","AMS1117-3.3","Package_TO_SOT_SMD:SOT-223-3_TabPin2","1","",""
